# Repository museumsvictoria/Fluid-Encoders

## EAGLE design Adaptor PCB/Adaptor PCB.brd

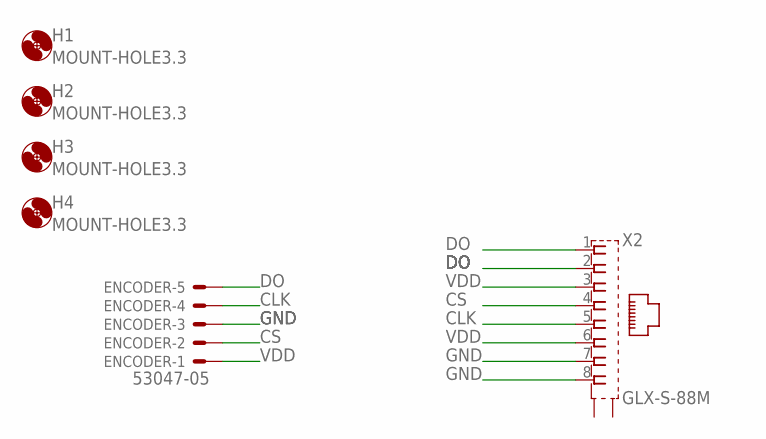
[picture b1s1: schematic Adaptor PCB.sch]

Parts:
ENCODER: 53047-05
H1, H2, H3, H4: MOUNT-HOLE3.3; 3,3
X2: GLX-S-88M

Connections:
CLK: ENCODER.4, X2.5
CS: ENCODER.2, X2.4
DO: ENCODER.5, X2.1, X2.2
GND: ENCODER.3, X2.7, X2.8
VDD: ENCODER.1, X2.3, X2.6

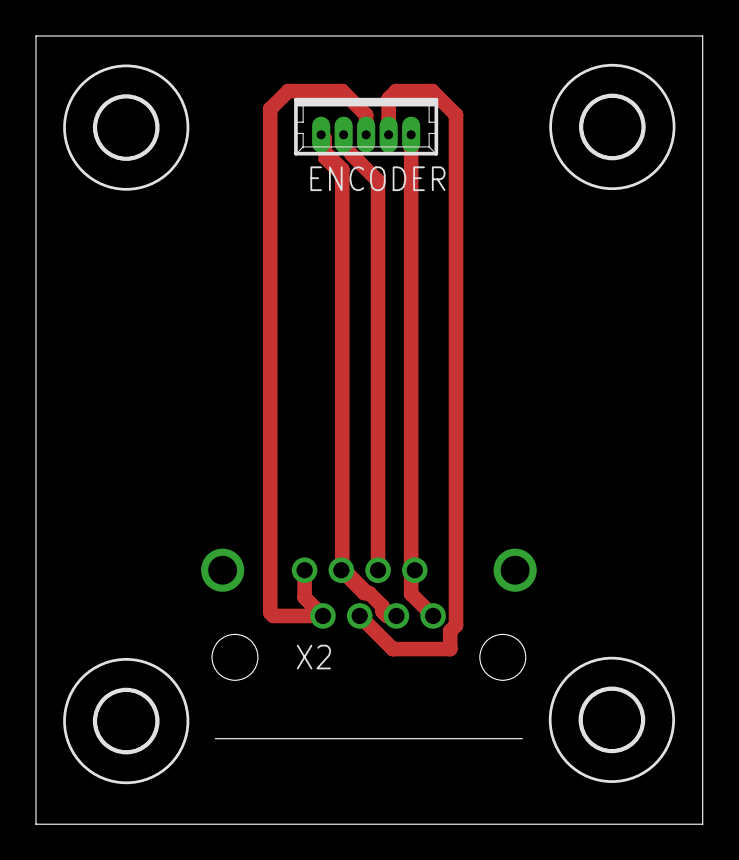
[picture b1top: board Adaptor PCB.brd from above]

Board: 2 copper layers, 37.0 x 43.8 mm, 6 parts (0 on the bottom side), 5 nets.

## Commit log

2018-07-04 folders
